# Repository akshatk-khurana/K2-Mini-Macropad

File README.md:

# K2-Mini-Macropad
A 4x4 macropad inspired by the Keychron K2.

## BOM
| Part | Quantity 
| --- | --- |
| Cherry MX switches | 16
| 1N4148 Diodes| 16 
| EC11 Encoder | 1
| PCB | 1 
| M3 16mm Screws | 5
| XIAO RP2040 | 1

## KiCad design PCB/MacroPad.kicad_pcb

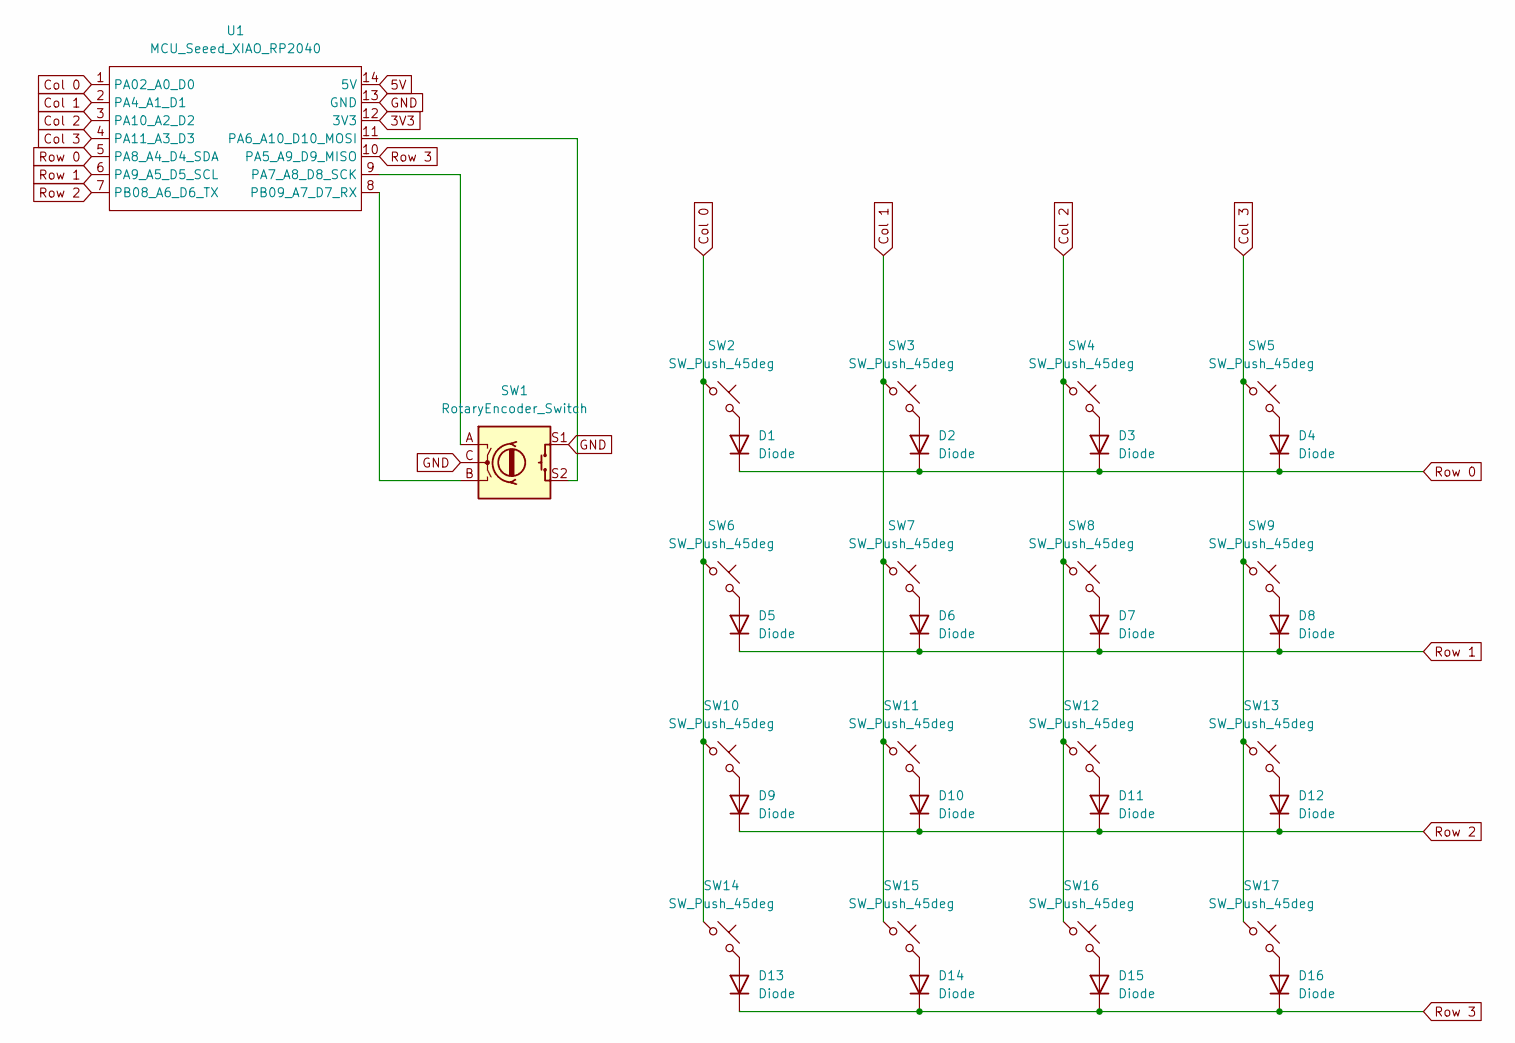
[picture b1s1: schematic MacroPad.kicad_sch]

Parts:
D1, D2, D3, D4, D5, D6, D7, D8, D9, D10, D11, D12, D13, D14, D15, D16: Diode; Diode_DO-35
SW1: RotaryEncoder_Switch; RotaryEncoder_Alps_EC11E-Switch_Vertical_H20mm
SW2, SW3, SW4, SW5, SW6, SW7, SW8, SW9, SW10, SW11, SW12, SW13, SW14, SW15, SW16, SW17: SW_Push_45deg; MX_PCB_1.00u
U1: MCU_Seeed_XIAO_RP2040; Seeed_XIAO_RP2040

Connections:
3V3: U1.12 (3V3)
5V: U1.14 (5V)
Col 0: SW2.1, SW6.1, SW10.1, SW14.1, U1.1 (PA02_A0_D0)
Col 1: SW3.1, SW7.1, SW11.1, SW15.1, U1.2 (PA4_A1_D1)
Col 2: SW4.1, SW8.1, SW12.1, SW16.1, U1.3 (PA10_A2_D2)
Col 3: SW5.1, SW9.1, SW13.1, SW17.1, U1.4 (PA11_A3_D3)
GND: SW1.C, SW1.S1, U1.13 (GND)
unnamed: D1.2 (A), SW2.2
unnamed: D2.2 (A), SW3.2
unnamed: D3.2 (A), SW4.2
unnamed: D4.2 (A), SW5.2
unnamed: D5.2 (A), SW6.2
unnamed: D6.2 (A), SW7.2
unnamed: D7.2 (A), SW8.2
unnamed: D8.2 (A), SW9.2
unnamed: D9.2 (A), SW10.2
unnamed: D10.2 (A), SW11.2
unnamed: D11.2 (A), SW12.2
unnamed: D12.2 (A), SW13.2
unnamed: D13.2 (A), SW14.2
unnamed: D14.2 (A), SW15.2
unnamed: D15.2 (A), SW16.2
unnamed: D16.2 (A), SW17.2
unnamed: SW1.S2, U1.11 (PA6_A10_D10_MOSI)
unnamed: SW1.A, U1.9 (PA7_A8_D8_SCK)
unnamed: SW1.B, U1.8 (PB09_A7_D7_RX)
Row 0: D1.1 (K), D2.1 (K), D3.1 (K), D4.1 (K), U1.5 (PA8_A4_D4_SDA)
Row 1: D5.1 (K), D6.1 (K), D7.1 (K), D8.1 (K), U1.6 (PA9_A5_D5_SCL)
Row 2: D9.1 (K), D10.1 (K), D11.1 (K), D12.1 (K), U1.7 (PB08_A6_D6_TX)
Row 3: D13.1 (K), D14.1 (K), D15.1 (K), D16.1 (K), U1.10 (PA5_A9_D9_MISO)

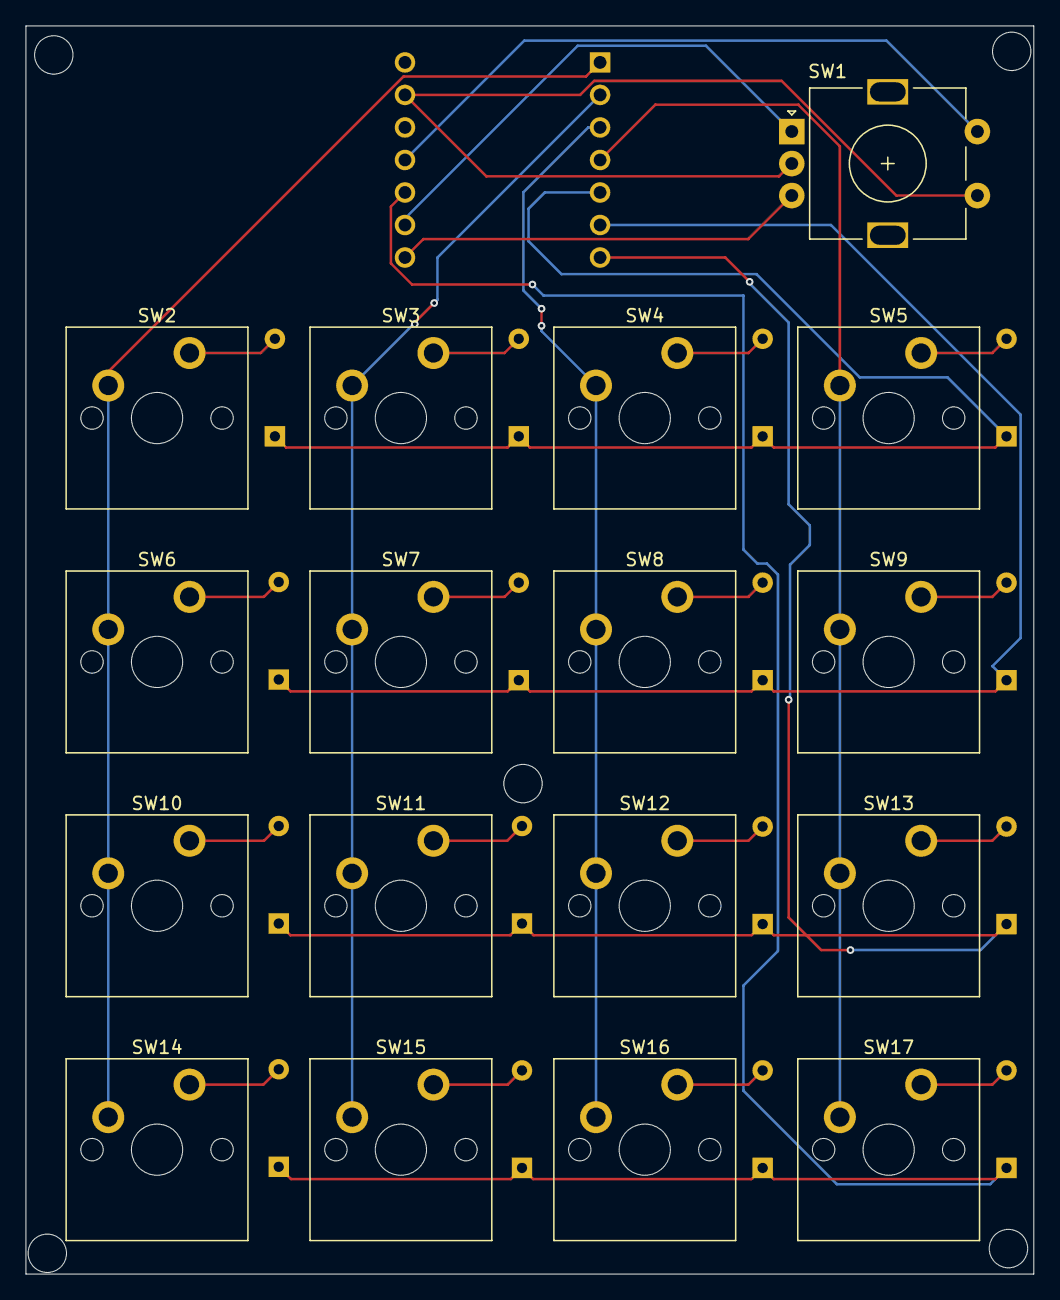
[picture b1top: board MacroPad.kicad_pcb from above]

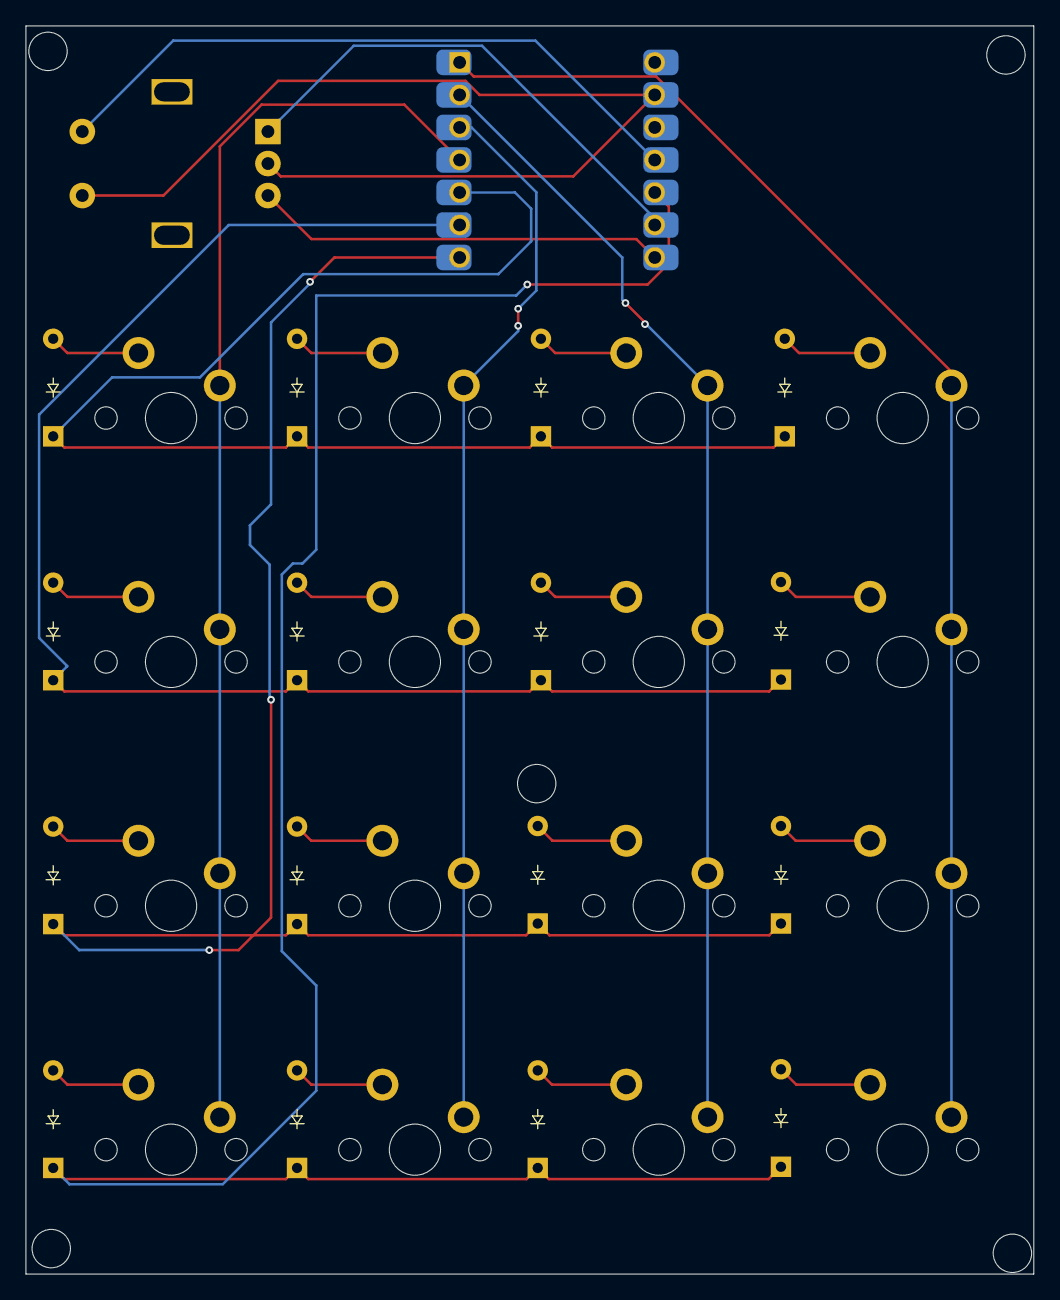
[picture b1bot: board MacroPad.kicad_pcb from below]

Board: 2 copper layers, 78.7 x 97.5 mm, 34 parts (17 on the bottom side), 28 nets.

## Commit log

2025-06-01 Schematic finished and PCB started
2025-06-02 Routed and finished PCB
2025-06-03 Finished the case and firmware
